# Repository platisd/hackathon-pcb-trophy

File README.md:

# Hackathon PCB trophy
A cool trophy for the winners of your Hackathon

## What?
This repository includes the necessary software and hardware schematics and layout files to create some trophy-shaped boards that can be given as awards to the winners of a competition/hackathon/task/you-name-it.

The trophies have are programmable, using the ATTiny85 microcontroller and have the ability to play a tune once a button is pressed.

## Why?
As someone who often gets involved in organizing hackathons I had to come up with cool looking trophies for our competitions' winners. 3D printed trophies take too long to be produced and assembled so I resorted to a different option: PCBs. Compared to the 3D printed trophies, a PCB is more durable, can be assembled faster, requires less equipment from your side (i.e. no printer needed) and looks - if not more - then equally as cool. More importantly, the trophy is programmable and has the potential to spark interest in electronics and hardware.

## How?
The circuit as well as the code are relatively straight forward. A microcontroller (ATTiny85) is connected to a buzzer and a tactile button is connected to the microcontroller's reset pin, causing the firmware to reboot every time it is pressed. Everything is powered up by a CR2032 coin cell battery.

On the software-side, the microcontroller plays an [RTTTL](https://en.wikipedia.org/wiki/Ring_Tone_Transfer_Language) tune (the [theme song from Rocky](https://www.youtube.com/watch?v=DhlPAj38rHc)) and then goes to deep sleep to preserve power. The RTTTL tune is played using code written by Brett Hagman from [Rogue Robotics](http://www.roguerobotics.com/).

### Components
* Hackathon trophy PCB ([Order it from PCBway.com](https://www.pcbway.com/project/shareproject/Hackathon_trophy.html))
* ATTiny85-20PU
* 12mm buzzer
* 4.7KΩ pull-up resistor
* 22Ω current limiting resistor
* 2032 coin cell battery holder
* 2032 coin cell battery

## Media
* [PCB trophies for your Hackathon](https://platis.solutions/blog/2018/05/16/pcb-trophies-for-your-hackathon/)
* [PCB trophies demo video](https://www.youtube.com/watch?v=lDynO2vfTys)

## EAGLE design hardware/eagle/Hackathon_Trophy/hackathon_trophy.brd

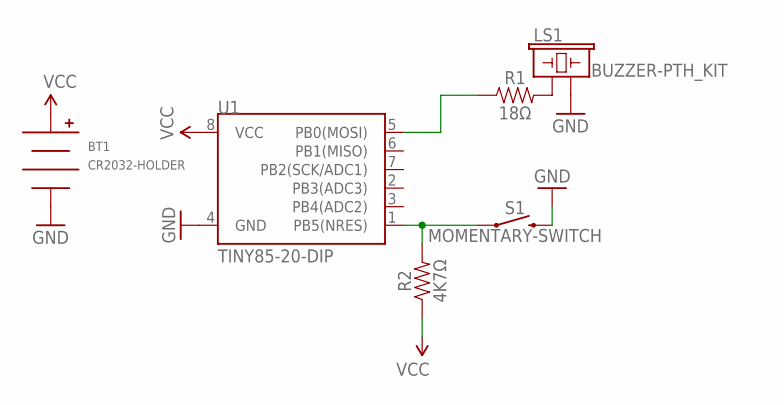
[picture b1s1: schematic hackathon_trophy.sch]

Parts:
BT1: CR2032-HOLDER; CH28-2032LF
LS1: BUZZER-PTH_KIT; BUZZER-12MM-KIT
R1: 18Ω; 1206
R2: 4K7Ω; 1206
S1: MOMENTARY-SWITCH; TACTILE_SWITCH_PTH_6.0MM_KIT
U1: TINY85-20-DIP; DIP08_MCU

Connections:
GND: BT1.NEG, LS1.- (2), S1.3 (2), U1.4 (GND)
unnamed: R2.2, S1.1, U1.1 (PB5(NRES))
unnamed: LS1.+ (1), R1.2
unnamed: R1.1, U1.5 (PB0(MOSI))
VCC: BT1.POS, R2.1, U1.8 (VCC)

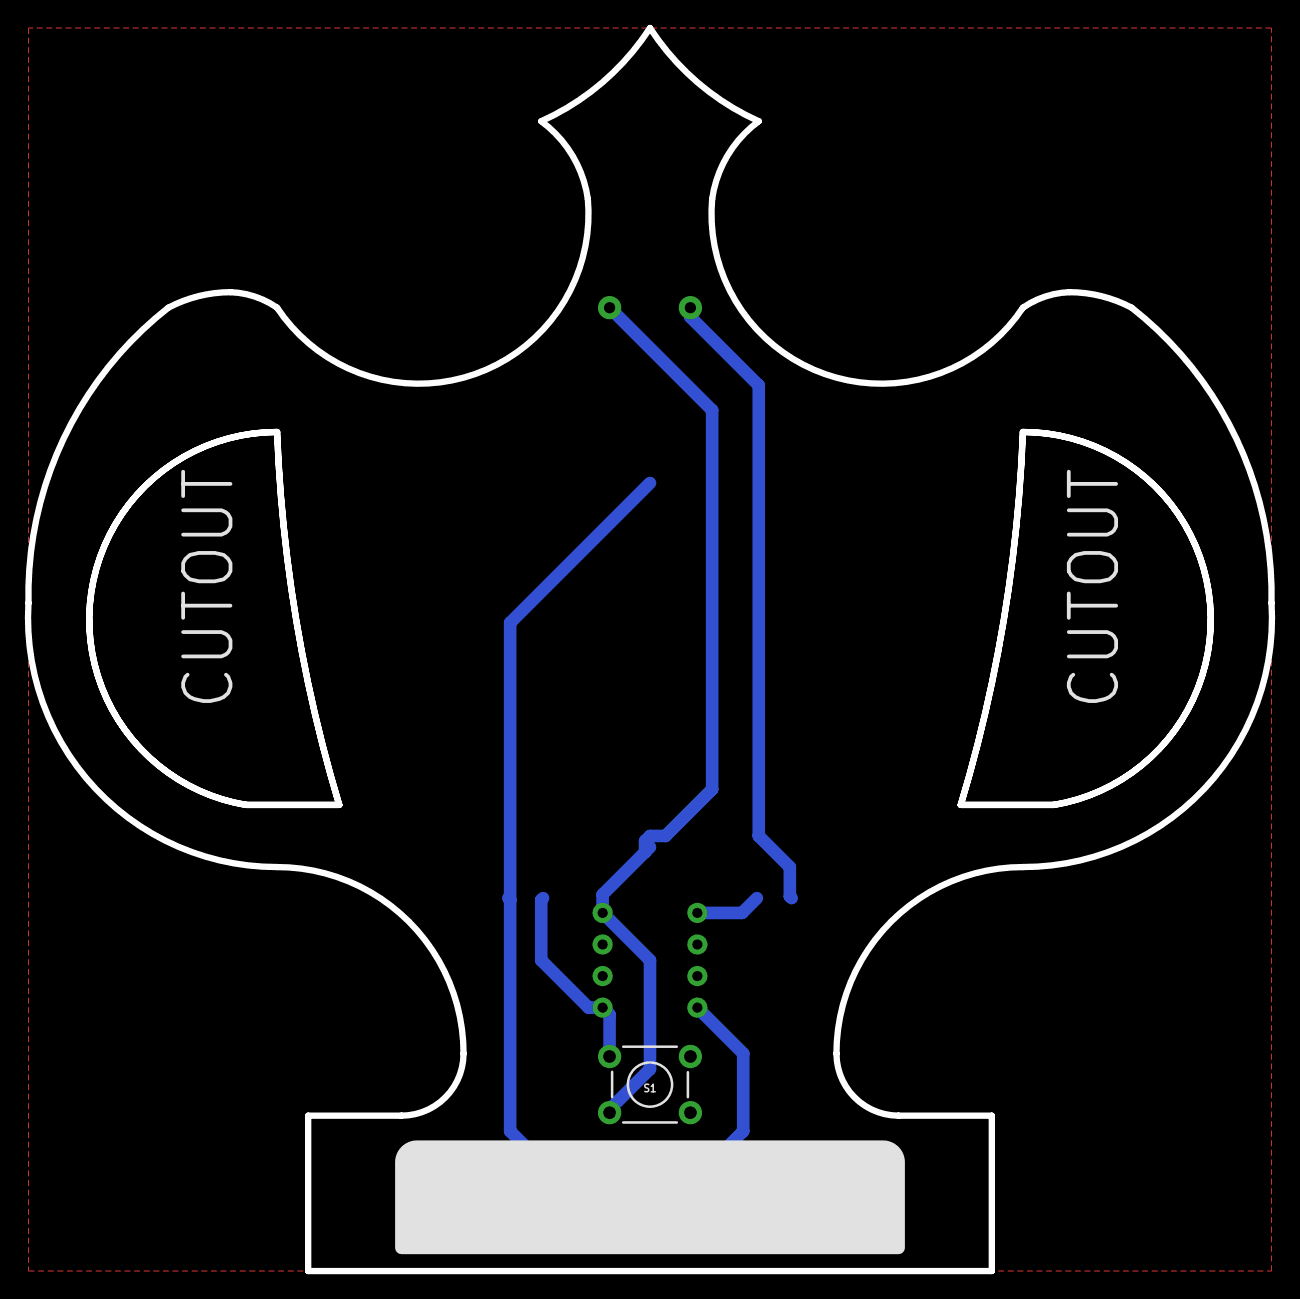
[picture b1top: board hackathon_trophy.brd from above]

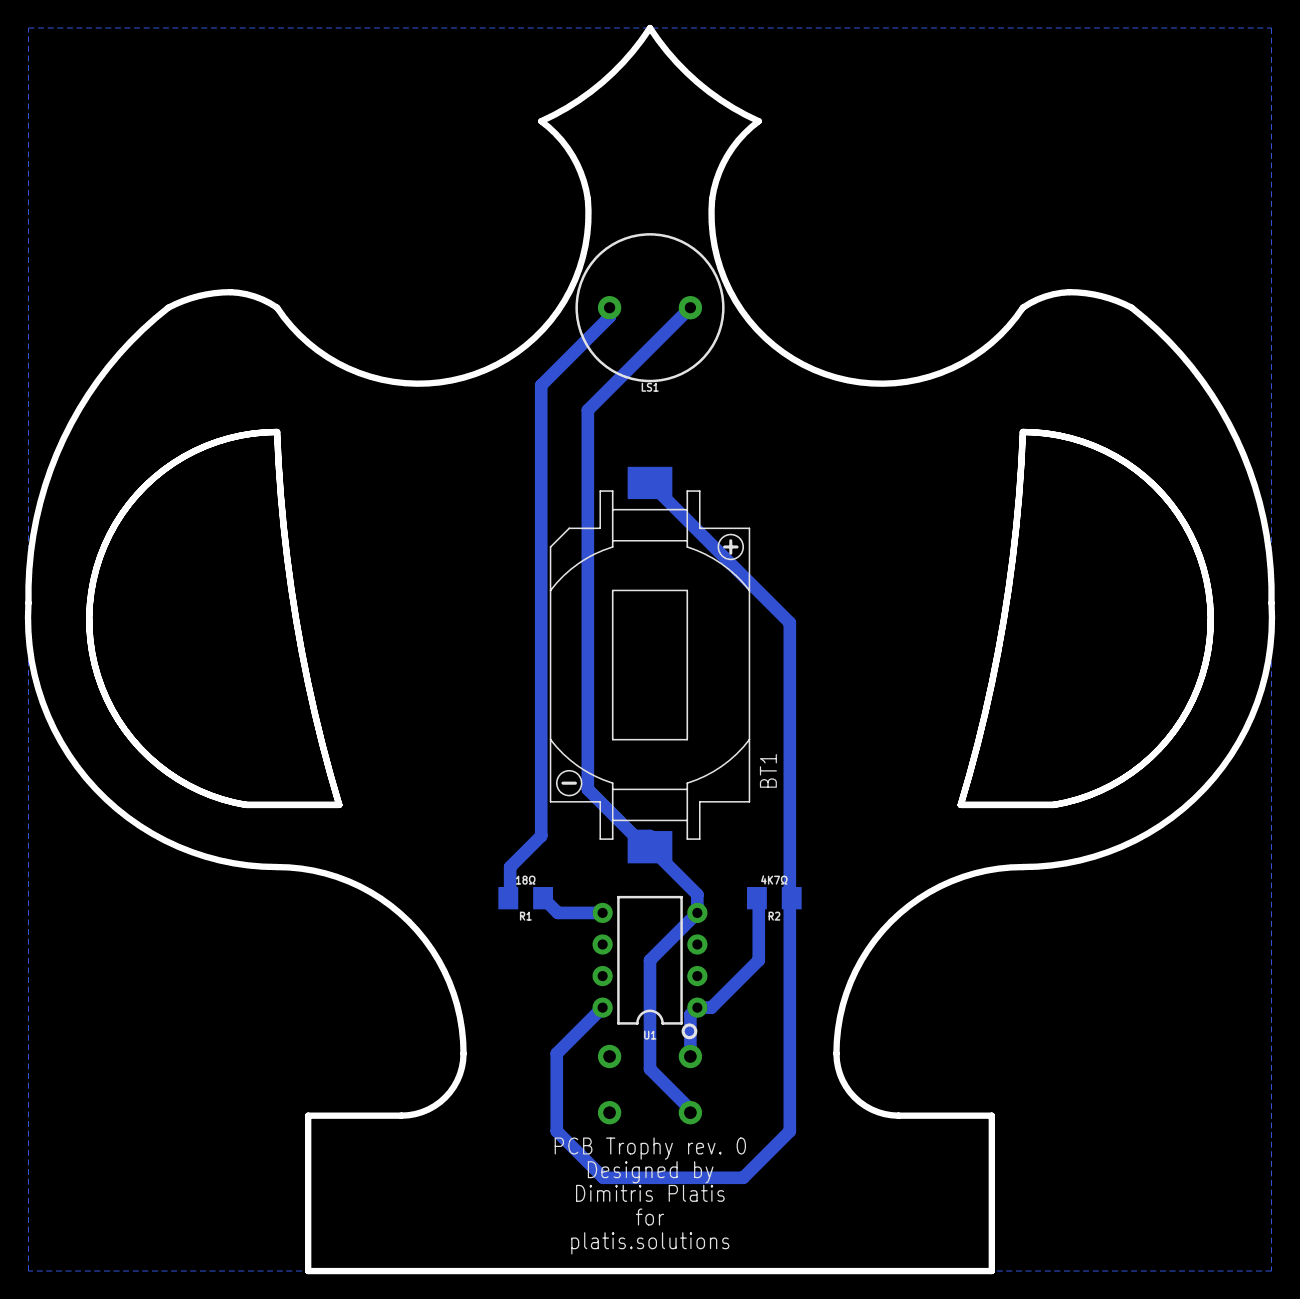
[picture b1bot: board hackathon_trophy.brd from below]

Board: 2 copper layers, 100.1 x 100.0 mm, 6 parts (5 on the bottom side), 5 nets.

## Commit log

2018-05-17 Add Arduino sketch
2018-05-17 Add rev.0 Eagle CAD schematics
2018-05-17 Add readme
2018-05-18 Fix circuit schematic
    The pull up was connected in series

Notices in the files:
parts and their libraries:
SparkFun-Retired: Licensing: Creative Commons ShareAlike 4.0 International - https://creativecommons.org/licenses/by-sa/4.0
